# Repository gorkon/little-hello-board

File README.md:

# little-hello-board

This is a very simple board, based on the ATtiny45 microcontroller. It has a button and two LEDs. One version has an FTDI connector for serial communications.

This is based on the PCB production processes and microcontroller programming taught in [Fab Academy](http://fabacademy.org/).

"You've taken your first step into a larger world" -Obi-Wan Kenobi (ANH)

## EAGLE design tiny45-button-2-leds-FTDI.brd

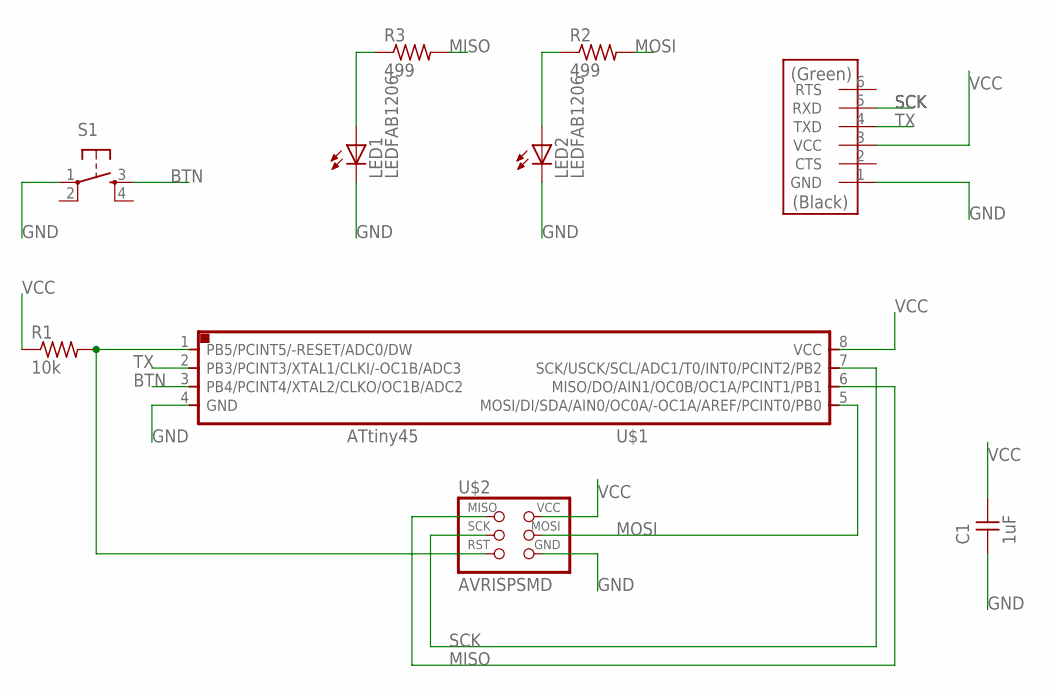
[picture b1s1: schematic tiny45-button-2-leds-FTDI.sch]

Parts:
C1: 1uF; C1206FAB
LED1, LED2: LEDFAB1206; LED1206FAB
R1: 10k; R1206FAB
R2, R3: 499; R1206FAB
S1: 6MM_SWITCH6MM_SWITCH; 6MM_SWITCH
U$1: ATTINY45SI; SOIC8
U$2: AVRISPSMD; 2X03SMD
U$3: FTDI-SMD-HEADER; 1X06SMD

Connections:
BTN: S1.3 (S), U$1.3 (PB4/PCINT4/XTAL2/CLKO/OC1B/ADC2)
GND: C1.1, LED1.2 (C), LED2.2 (C), S1.1, U$1.4 (GND), U$2.6 (GND), U$3.1 (GND)
MISO: R3.2, U$1.6 (MISO/DO/AIN1/OC0B/OC1A/PCINT1/PB1), U$2.1 (MISO)
MOSI: R2.2, U$1.5 (MOSI/DI/SDA/AIN0/OC0A/-OC1A/AREF/PCINT0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), U$2.4 (MOSI)
unnamed: LED1.1 (A), R3.1
unnamed: LED2.1 (A), R2.1
unnamed: R1.2, U$1.1 (PB5/PCINT5/-RESET/ADC0/DW), U$2.5 (RST)
SCK: U$1.7 (SCK/USCK/SCL/ADC1/T0/INT0/PCINT2/PB2), U$2.3 (SCK), U$3.5 (RXD)
TX: U$1.2 (PB3/PCINT3/XTAL1/CLKI/-OC1B/ADC3), U$3.4 (TXD)
VCC: C1.2, R1.1, U$1.8 (VCC), U$2.2 (VCC), U$3.3 (VCC)

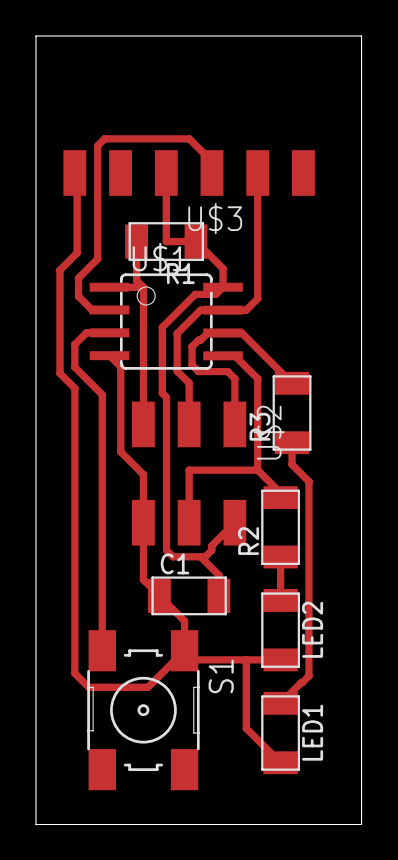
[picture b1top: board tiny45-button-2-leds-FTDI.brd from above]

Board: 2 copper layers, 18.1 x 43.8 mm, 10 parts (0 on the bottom side), 10 nets.

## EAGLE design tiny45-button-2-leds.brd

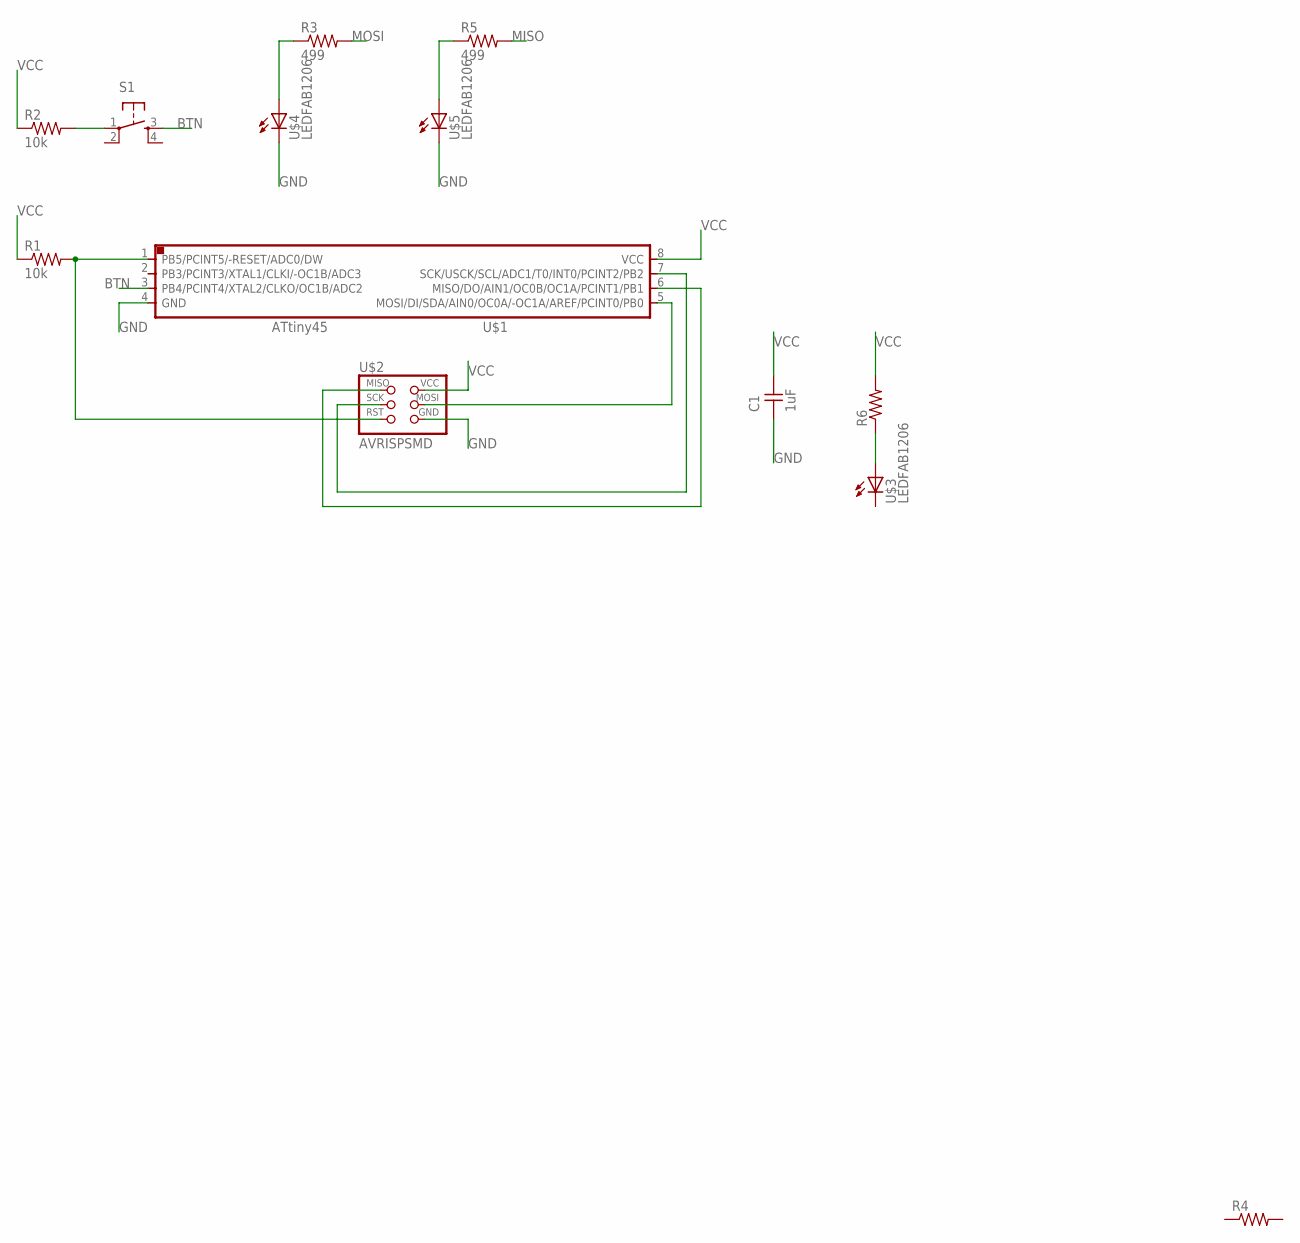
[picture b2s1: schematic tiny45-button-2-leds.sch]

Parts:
C1: 1uF; C1206FAB
R1, R2: 10k; R1206FAB
R3, R5: 499; R1206FAB
R4, R6: RES-US1206FAB; R1206FAB
S1: 6MM_SWITCH6MM_SWITCH; 6MM_SWITCH
U$1: ATTINY45SI; SOIC8
U$2: AVRISPSMD; 2X03SMD
U$3, U$4, U$5: LEDFAB1206; LED1206FAB

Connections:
BTN: S1.3 (S), U$1.3 (PB4/PCINT4/XTAL2/CLKO/OC1B/ADC2)
GND: C1.1, R6.1, U$1.4 (GND), U$2.6 (GND), U$3.1 (A), U$4.2 (C), U$5.2 (C)
MISO: R5.2
MOSI: R3.2
unnamed: R5.1, U$5.1 (A)
unnamed: R2.2, S1.1
unnamed: R3.1, U$4.1 (A)
unnamed: U$1.5 (MOSI/DI/SDA/AIN0/OC0A/-OC1A/AREF/PCINT0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), U$2.4 (MOSI)
unnamed: U$1.7 (SCK/USCK/SCL/ADC1/T0/INT0/PCINT2/PB2), U$2.3 (SCK)
unnamed: U$1.6 (MISO/DO/AIN1/OC0B/OC1A/PCINT1/PB1), U$2.1 (MISO)
unnamed: R1.2, U$1.1 (PB5/PCINT5/-RESET/ADC0/DW), U$2.5 (RST)
VCC: C1.2, R1.1, R2.1, R6.2, U$1.8 (VCC), U$2.2 (VCC)

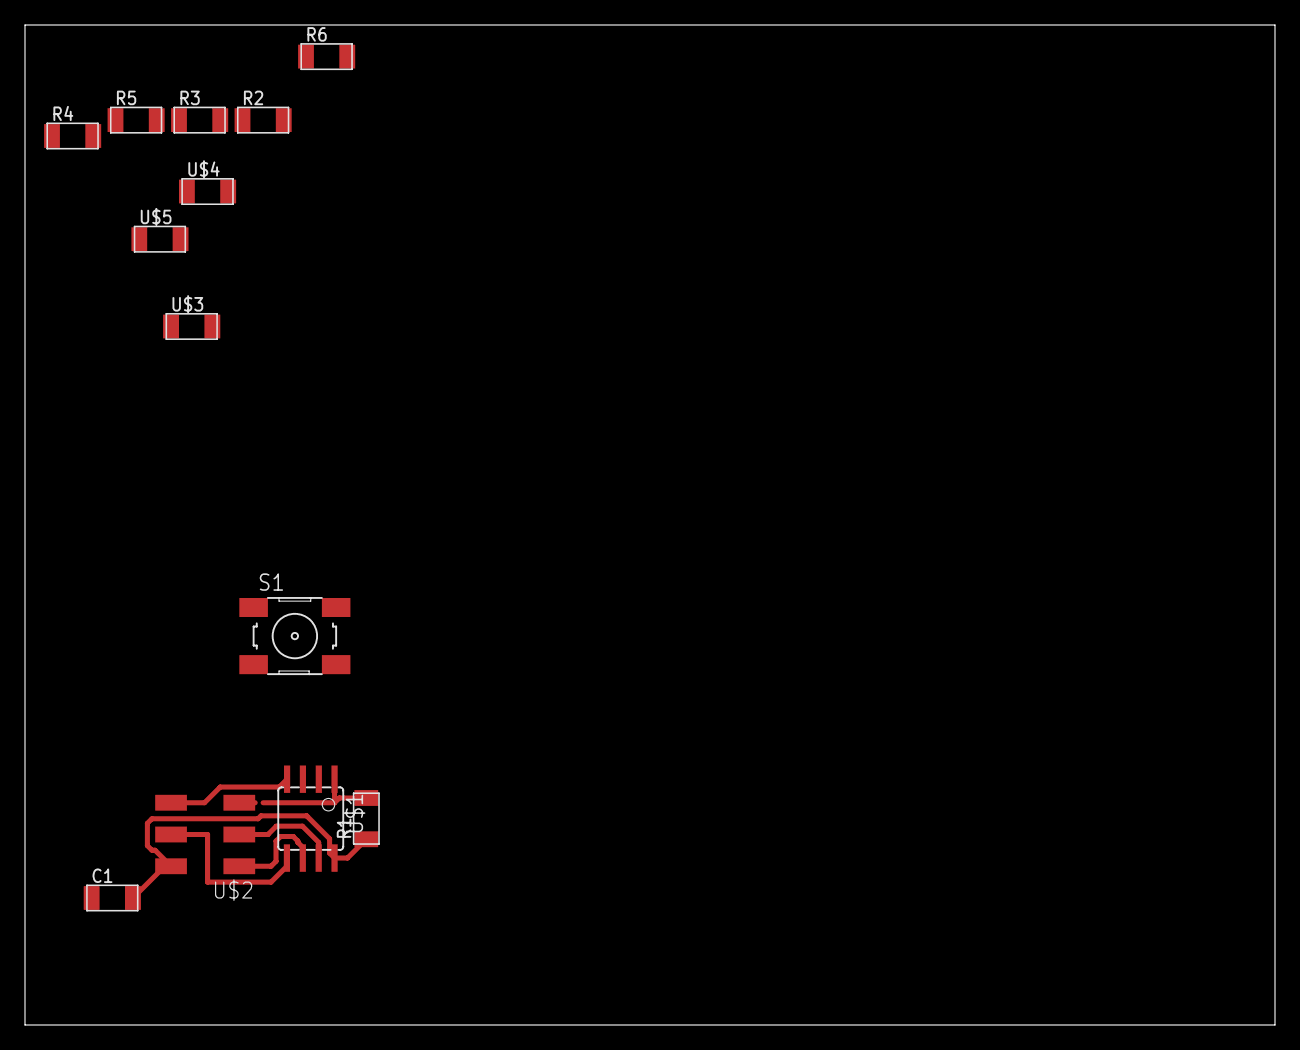
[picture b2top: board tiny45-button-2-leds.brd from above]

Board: 2 copper layers, 100.0 x 80.0 mm, 13 parts (0 on the bottom side), 10 nets.

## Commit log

2019-05-22 add initial readme
2019-05-22 upload files for simplest board and simple-FTDI
2019-05-22 remove autosaves
2019-05-23 add arduino sketches
